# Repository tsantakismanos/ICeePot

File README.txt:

ICeePot 

GOAL
ICeePot solution is a way to help remotely accessing and managing pot moisture information. It combines several server-client technologies to gather, organize and provide moisture information in clients PC and mobile phones.

HIERARCHY
ICeePot follows the server-client architecture with the one (or several) pot server performing and saving moisture measurements and one or several mobile or desktop applications responsible for presenting moisture graphs per pot.

PROJECTS:
ICeePot/software folder contains the various projects implementing the Solutions functionality:
 - ICeePotServer: This is basically the source code of an arduino ethernet board. It reads the moisture condition from analog     pins &        saves this information on its SD card.
 - ICeePotLib: This is a library project and cointains the entities and tools used in the client Projects. It's a java project that uses        gradle to add itself in the local repository. 
 - ICeePotPC: This is a java application acting as an ICeePot client. It provides a UI to display moisture information and has dependencies    on ICeePotLib
 - ICeePotMobile: This is another ICeePot client implemented as an android application. It depens on ICeePotLib as well and provides           moisture aggregated information.
 - ICeePotWeb: This is soon to be another ICeePot client aimed to act as both a web UI and a API of the ICeePotServer. It will provide a REST API for ICeePotPC and ICeePotMobile clients which now contact directly ICeePotServer with the use of ICeePotLib

DOCUMENTATION:
ICeePot/documentation folder contains useful notes, diagrams about the project
  - notes: about tools used, code explanations, etc 
  - diagrams: flows, schematics, class diagrams, etc

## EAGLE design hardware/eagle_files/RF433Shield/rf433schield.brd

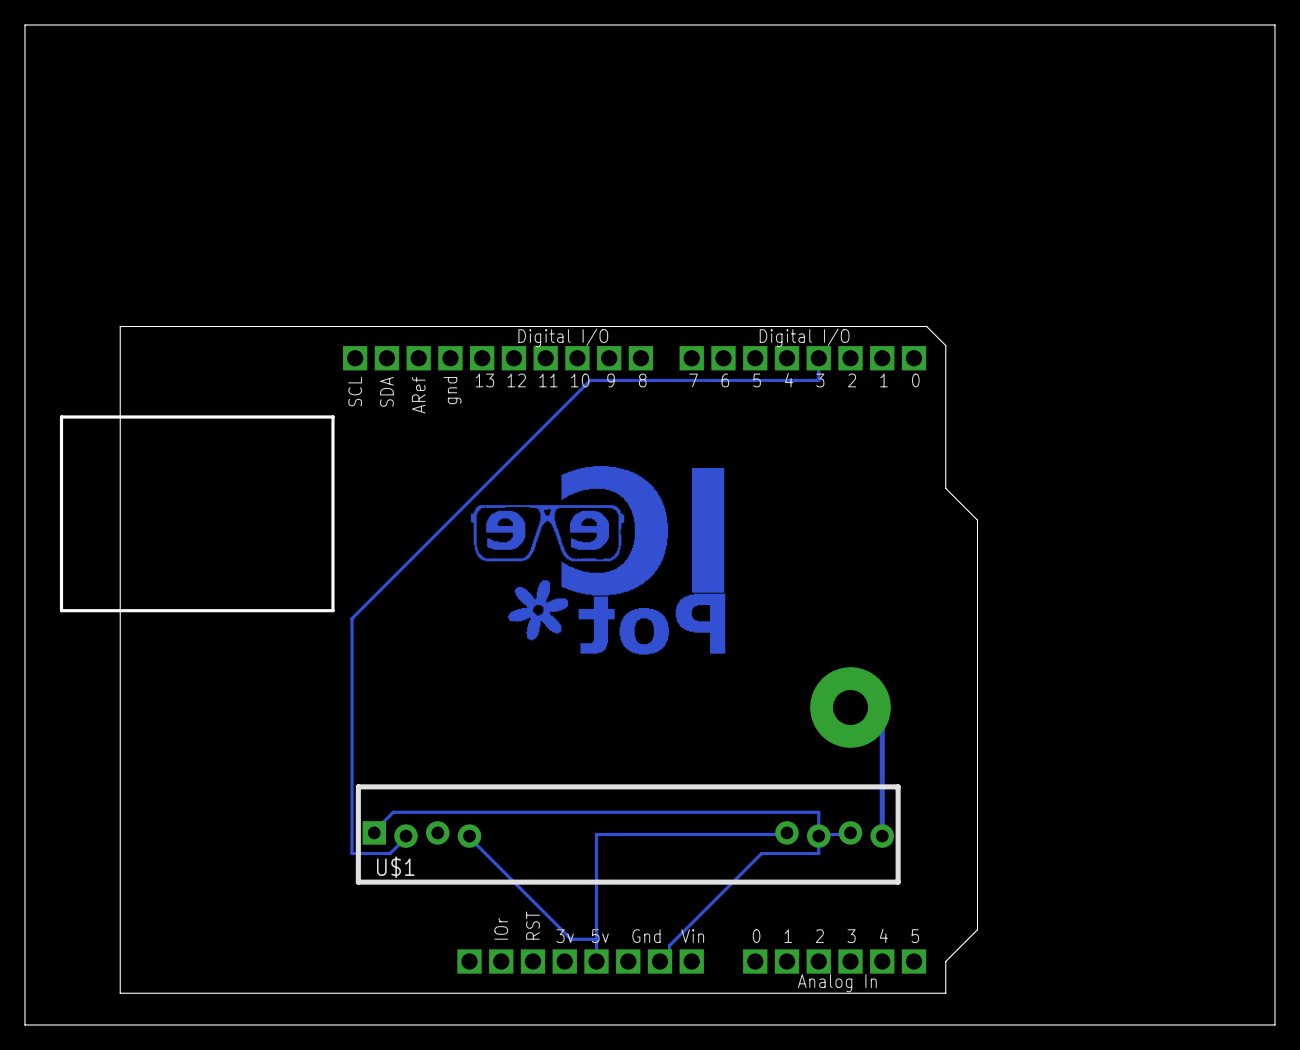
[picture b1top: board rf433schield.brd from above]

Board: 2 copper layers, 100.0 x 80.0 mm, 3 parts (0 on the bottom side), 3 nets.

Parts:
E$1: ICEEPOT_LOGO_REV
U1: ARDUINOR3-DIMENSION; ARDUINOR3
U$1: RF-LINK_RX

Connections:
unnamed: U1.D3, U$1.DATA@1
unnamed: U1.5V, U$1.+5V@1, U$1.+5V@2
unnamed: U1.GND1, U$1.GND@1, U$1.GND@2, U$1.GND@3

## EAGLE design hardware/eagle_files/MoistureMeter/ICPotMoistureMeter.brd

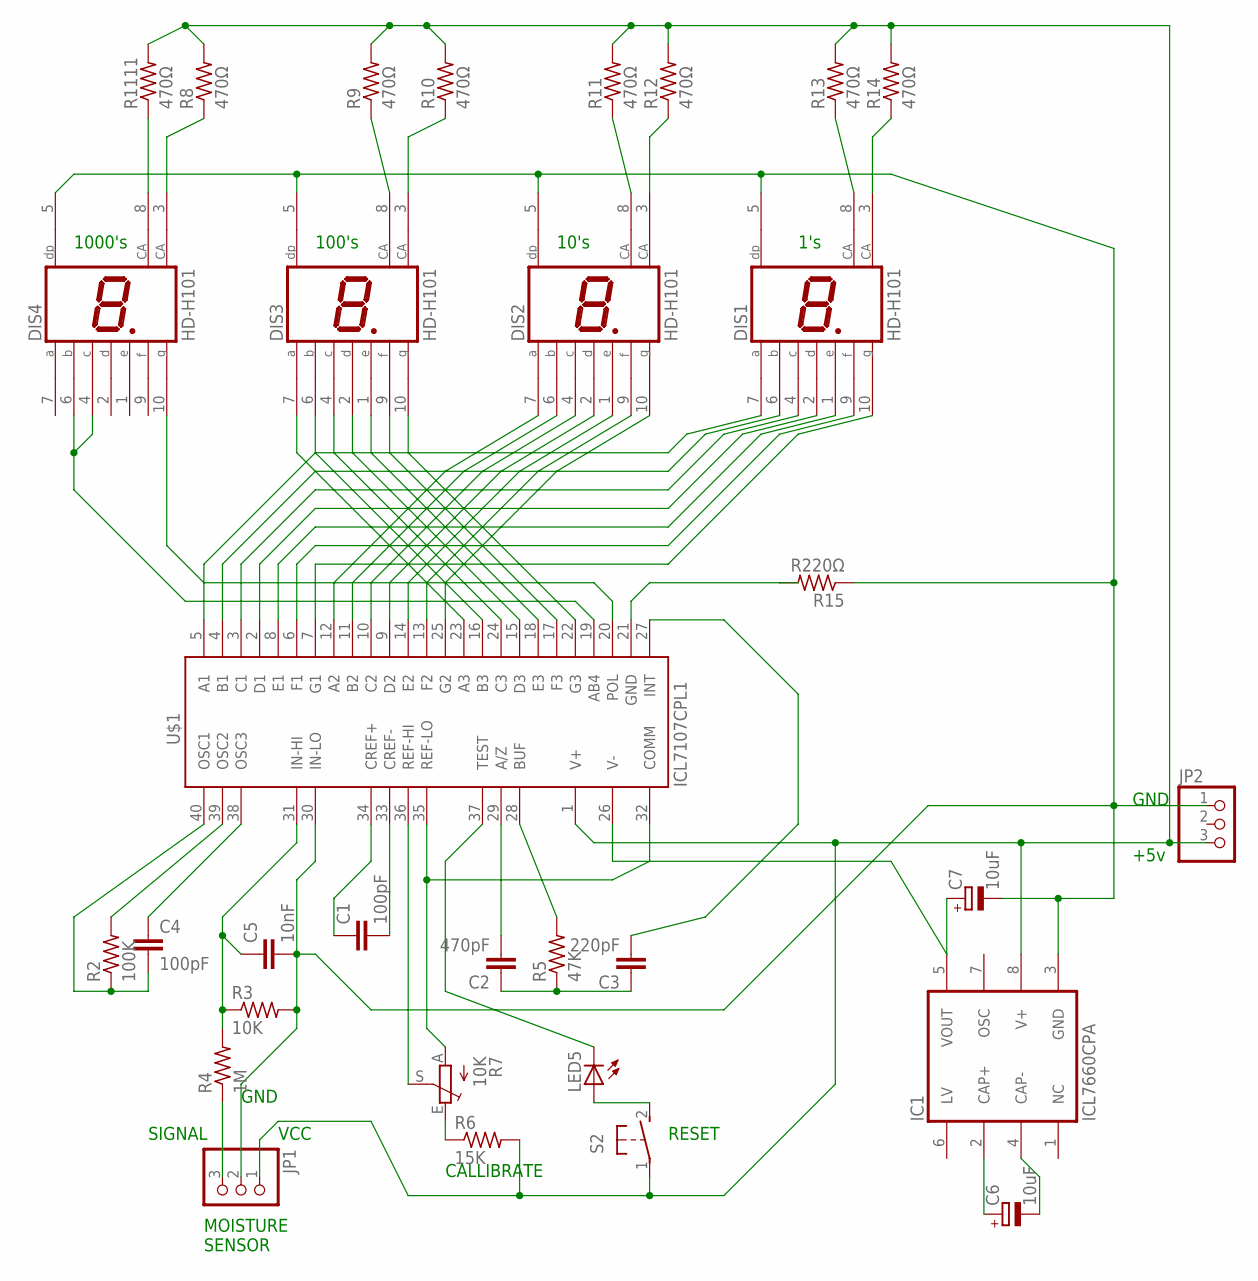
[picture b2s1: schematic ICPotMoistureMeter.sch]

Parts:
C1, C4: 100pF; C025-024X044
C2: 470pF; C025-024X044
C3: 220pF; C025-024X044
C5: 10nF; C025-024X044
C6, C7: 10uF; E2-5
DIS1, DIS2, DIS3, DIS4: HD-H101; HDSP-M
IC1: ICL7660CPA; DIL08
JP1, JP2: PINHD-1X3/90; 1X03/90
LED5: LED3MM
R2: 100K; 0204V
R3: 10K; 0204V
R4: 1M; 0204V
R5: 47K; 0204V
R6: 15K; 0204V
R7: 10K; CA6V
R8, R9, R10, R11, R12, R13, R14, R1111: 470Ω; 0204V
R15: R220Ω; 0204V
S2: 31-XX; B3F-31XX
U$1: ICL7107CPL1; DIL40

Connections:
unnamed: DIS1.7 (A), U$1.5 (A1)
unnamed: DIS1.6 (B), U$1.4 (B1)
unnamed: DIS1.4 (C), U$1.3 (C1)
unnamed: DIS1.2 (D), U$1.2 (D1)
unnamed: DIS1.1 (E), U$1.8 (E1)
unnamed: DIS1.9 (F), U$1.6 (F1)
unnamed: DIS1.10 (G), U$1.7 (G1)
unnamed: R2.2, U$1.39 (OSC2)
unnamed: C1.1, U$1.34 (CREF+)
unnamed: DIS2.7 (A), U$1.12 (A2)
unnamed: C5.1, R3.1, R4.2, U$1.31 (IN-HI)
unnamed: DIS2.6 (B), U$1.11 (B2)
unnamed: DIS2.4 (C), U$1.10 (C2)
unnamed: JP1.3, R4.1
unnamed: DIS2.2 (D), U$1.9 (D2)
unnamed: DIS2.1 (E), U$1.14 (E2)
unnamed: DIS2.9 (F), U$1.13 (F2)
unnamed: DIS2.10 (G), U$1.25 (G2)
unnamed: DIS3.7 (A), U$1.23 (A3)
unnamed: DIS3.6 (B), U$1.16 (B3)
unnamed: C1.2, U$1.33 (CREF-)
unnamed: DIS3.4 (C), U$1.24 (C3)
unnamed: DIS3.2 (D), U$1.15 (D3)
unnamed: DIS3.1 (E), U$1.18 (E3)
unnamed: DIS3.9 (F), U$1.17 (F3)
unnamed: DIS3.10 (G), U$1.22 (G3)
unnamed: C4.2, R2.1, U$1.40 (OSC1)
unnamed: DIS4.4 (C), DIS4.6 (B), U$1.19 (AB4)
unnamed: DIS4.10 (G), U$1.20 (POL)
unnamed: DIS4.8 (CA), R1111.1
unnamed: C3.2, U$1.27 (INT)
unnamed: DIS4.3 (CA), R8.1
unnamed: DIS3.8 (CA), R9.1
unnamed: DIS3.3 (CA), R10.1
unnamed: R5.2, U$1.28 (BUF)
unnamed: C4.1, U$1.38 (OSC3)
unnamed: C2.1, C3.1, R5.1
unnamed: C2.2, U$1.29 (A/Z)
unnamed: C7.+, IC1.5 (VOUT), U$1.26 (V-)
unnamed: C5.2, C7.-, DIS1.5 (DP), DIS2.5 (DP), DIS3.5 (DP), DIS4.5 (DP), IC1.3 (GND), JP1.2, JP2.1, R3.2, R15.1, U$1.30 (IN-LO)
unnamed: R7.A, U$1.32 (COMM), U$1.35 (REF-LO)
unnamed: R7.S, U$1.36 (REF-HI)
unnamed: LED5.K (C), U$1.37 (TEST)
unnamed: R6.1, R7.E
unnamed: DIS2.8 (CA), R11.1
unnamed: DIS2.3 (CA), R12.1
unnamed: DIS1.8 (CA), R13.1
unnamed: DIS1.3 (CA), R14.1
unnamed: LED5.A, S2.2 (S)
unnamed: R15.2, U$1.21 (GND)
unnamed: IC1.8 (V+), JP1.1, JP2.3, R6.2, R8.2, R9.2, R10.2, R11.2, R12.2, R13.2, R14.2, R1111.2, S2.1, U$1.1 (V+)
unnamed: C6.+, IC1.2 (CAP+)
unnamed: C6.-, IC1.4 (CAP-)

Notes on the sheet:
GND
VCC
SIGNAL
+5v
MOISTURE SENSOR
1's
10's
100's
1000's
CALLIBRATE
RESET

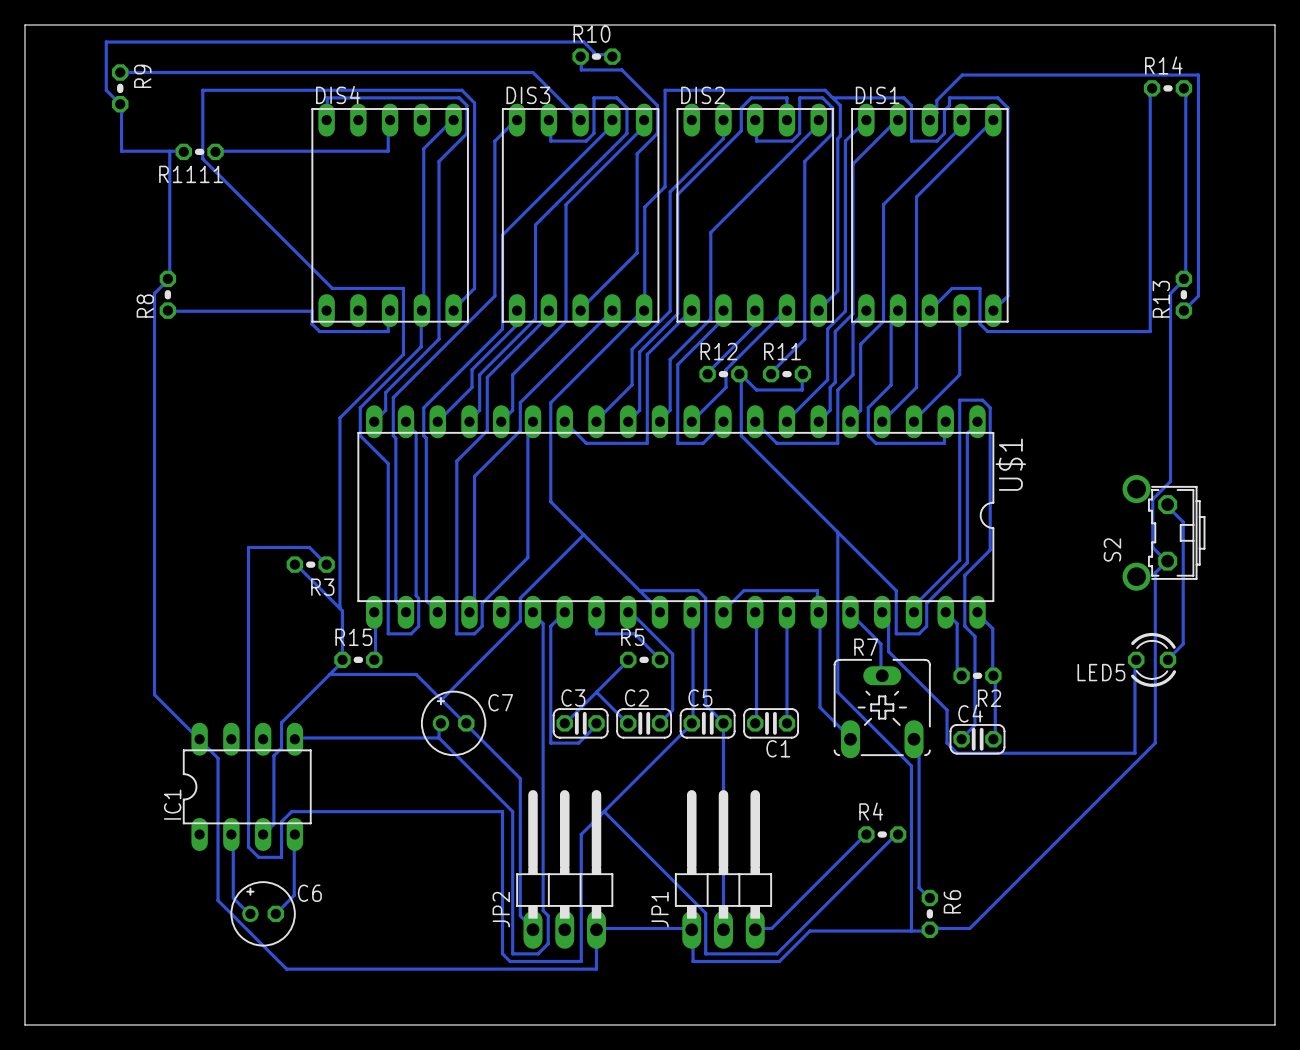
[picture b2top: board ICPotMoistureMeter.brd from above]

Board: 2 copper layers, 100.0 x 80.0 mm, 32 parts (0 on the bottom side), 53 nets.

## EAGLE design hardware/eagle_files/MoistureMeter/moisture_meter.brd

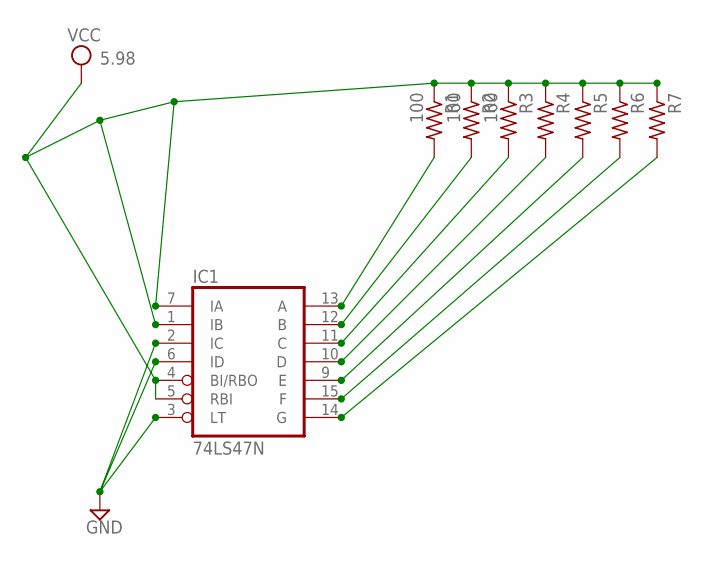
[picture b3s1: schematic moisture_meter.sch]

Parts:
IC1: 74LS47N; DIL16
R1, R2, R3: 100; 0207/10
R4, R5, R6, R7: R-US_0207/10; 0207/10

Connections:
GND: IC1.2 (IC), IC1.3 (LT), IC1.6 (ID), IC1.8 (GND)
unnamed: IC1.13 (A), R1.2
unnamed: IC1.12 (B), R2.2
unnamed: IC1.11 (C), R3.2
unnamed: IC1.10 (D), R4.2
unnamed: IC1.9 (E), R5.2
unnamed: IC1.15 (F), R6.2
unnamed: IC1.14 (G), R7.2
VCC: IC1.1 (IB), IC1.4 (BI/RBO), IC1.5 (RBI), IC1.7 (IA), IC1.16 (VCC), R1.1, R2.1, R3.1, R4.1, R5.1, R6.1, R7.1

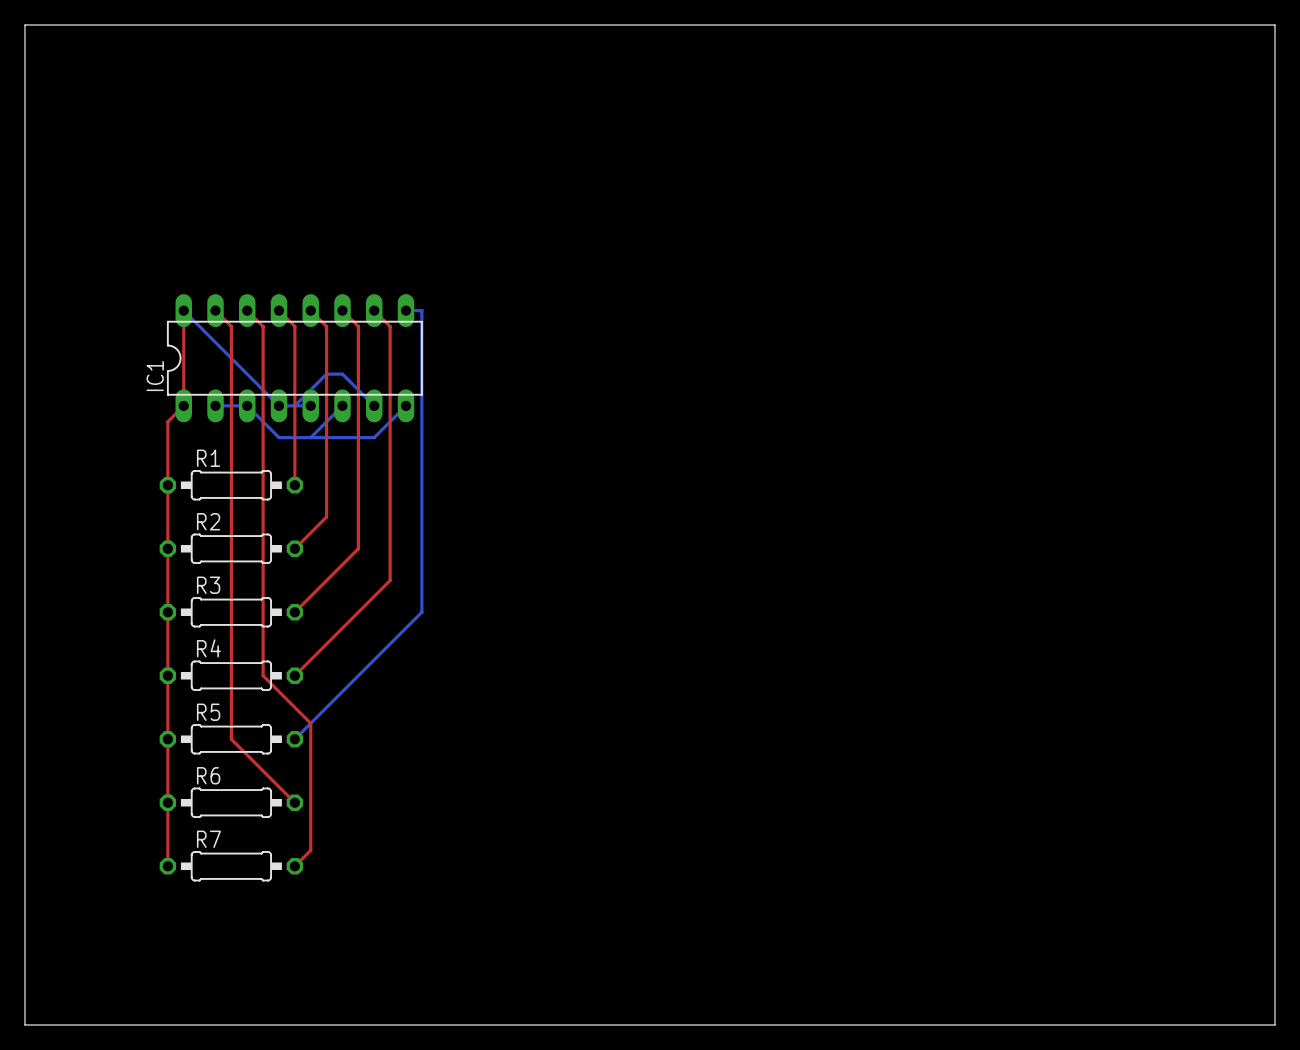
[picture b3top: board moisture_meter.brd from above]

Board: 2 copper layers, 100.0 x 80.0 mm, 8 parts (0 on the bottom side), 9 nets.

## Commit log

2013-01-16 tsantakis manos: initial commit
2013-01-16 tsantakismanos : test commit
2013-01-16 tsantakismanos: README added
2013-01-16 tsantakismanos added the first server sketch with no time synchronization
2013-01-16 tsantakismanos: arduino sketch & README
2013-01-17 tsantakismanos: README updated
2013-01-17 README updated
2013-01-17 diagram remote
2013-01-17 1 diagram removed
2013-01-17 tsantakismanos: diagrams/logos added
2013-01-17 documentation updates
2013-01-17 tsantakismanos: minor variable definitions changes in server
2013-01-17 tsantakismanos: ICeePot implemented in java swing
2013-01-18 tsantakismanos: modifications
2013-01-18 tsantakismanos: documentation updated
2013-01-18 added a single line as a suggestion for a new section in our documentation
2013-01-18 tsantakismanpos: documentation updated
2013-01-18 squash! Revert "added a single line as a suggestion for a new section in our documentation"
2013-01-18 Merge branch 'master' of https://github.com/tsantakismanos/ICeePot
    Conflicts:
    documentation/notes/git.odt
2013-01-18 tsantakismanos: files removed
2013-01-18 added the eagle project for the Moisture Meter
2013-01-18 git notes updated
2013-01-18 swing client implemented
2013-01-19 changes in software workspace file organizing
2013-01-21 swing_client mockup added
2013-01-23 changes in subproject names
2013-01-24 diagrams added
2013-01-24 diagrams added & others renamed
2013-01-25 ICeePotServer flow diagram modified
2013-01-25 measurement files are now organized in date basis (1 per month) and the files are named after that day
2013-01-25 modifications for better printing result
2013-02-01 diagram updates with new ideas about client-server messages
2013-02-01 PC client mock-up modified
2013-02-02 client now sends the desired date to server instead of dummy messages
2013-02-02 time interval between measurements changed to 15 minutes
2013-02-02 Time and NTP libraries added to the project
2013-02-04 Server time synchronized manually. File in which server stores files changed to Day|hour:minutes:sec|pin|value
2013-02-06 server is now able to time-synchronize itself at the beggining of the sketch
2013-02-07 ICeePotPC: a package created to model the server communication and the UI package modified to meet this change
2013-02-07 small modification in variable names
2013-02-07 custom NTP library updated to time-sunchronize the server
2013-02-08 documentation: organized diagrams to folders
2013-02-12 Date selectors added to MainWindow & Alert Dialog added
2013-02-12 debug precompiler declaration removed
2013-02-12 first request to server with dates set from MainWindow
2013-02-13 new pots added, and alerts
2013-02-13 minor bugs in message parsing
2013-02-13 minor bug in message parsing
2013-02-13 unnecessary file
2013-02-14 Results area moved into a Scrollable Pane
2013-02-14 main window set to non-resizable
2013-02-14 pot panel is now the swing entity to be displayed in every tab
2013-02-14 interval in server changed to 20 mins
2013-02-14 last measurement text boxes enabled
2013-02-15 chart creation
2013-02-17 comments removed, debug options added in context for showing/hiding the results panel and from-to dates information retrieval from server is now available
2013-02-17 return nothing is month info not available
2013-02-19 adding pots & server settings now moved to a config file. Adding pots is now possible
2013-02-19 icon into jar, exception handling in addpot, change server
2013-02-19 debug-->false, time interval=60min
2013-02-20 changed the format in latest measurement date
2013-02-20 dateformat variable for potpanel as class variable, textresults now show the whole date
2013-02-21 handler added for dropdowns be more responsive and window sizes changed
2013-02-22 sanity checks if pots are available in the settings.file
2013-02-22 Dynamical adding tabs when NewPot is done. This is done with the use of Observer pattern to MainWIndow
2013-02-22 Context object now follows the Singleton pattern, class diagram also added
2013-02-27 resizable UI
2013-02-27 settings xml creation if non-existent in the beginning
2013-02-27 bug fixed, now measurements are fetched per pot analog pin (not all)
2013-02-27 resized the results list text area
2013-02-27 resizings..
2013-02-28 settings.xml with no caps and Jchart panel resizable to both directions
2013-02-28 new jar
2013-03-01 bug fixed txtresults gets cleared in every "Get info" click
2013-03-01 server sketch (minor TODOs), new client jar
2013-03-06 separate thread in PotPanel UI for request execution, progressbar added and min - max series added to chart
2013-03-08 progressbar shows real progress, closings in window more efficient
2013-03-08 server can now update its time periodically
2013-03-08 settings shouldn't be in repository
2013-03-08 settings.xml to be ignored from now on
2013-03-12 slidebars added to pot panels for setting min/max moist values, Server timeout also in settings
2013-03-12 Handling for settings xml moved from context to a special Settings class, Exception handling changed in context class
2013-03-12 minor bug fixed on the slidebars size, hostname is not validated in settings dialog
2013-03-12 Application jar moved to bin folder (unversioned)
2013-03-12 server request done from separate thread of the newly class ThreadService
2013-03-14 appication packege renamed to application
2013-03-14 ServerService run method now passes an Exception to its caller if the request itself throws one
2013-03-22 server connection modifications
2013-03-22 the schematic for RF shield which will be the RF interface of the arduino server
2013-03-22 unnecessary handler removed
2013-03-31 Pin concept replaced with id one. Fixed bug to update the moist values of the right pot
2013-04-03 wireless mode added to server sketch, virtual library added and chart jar added to client
2013-04-11 COntext passing as argument replaced with calls to static getInstance method
2013-04-11 Pot object removed from UI elements and now only Context keeps them in an Array, providing methods for accessing them to UI
2013-04-11 Pot concept in server package turned to potId (just renaming).
2013-04-11 server sketch and swing client changed to store/receive/parse binary packets instead of text ones. Type of measurement also added as a concept
2013-04-11 changes to documentation
2013-04-12 bugs fixed, comments removed, time server changed
2013-04-12 bug fixed: in packet receiving
2013-04-12 pot creation moved from NewPotDialog to Context method, check if ID given is unique
2013-04-12 server script to migrate text measures to binary ones
2013-04-12 bugs in migr script
2013-04-13 migration script executed
2013-04-13 migration script final
2013-04-14 unnecessary swing component variables removed after code review
2013-04-17 remove pot funcitonality added
2013-04-19 Simple/Detail view mode added
2013-04-28 Latest schematic updates and the pcb design
2013-04-28 rfshield and transmitter schematics added
2013-04-28 rfshield and tansmitter added
2013-04-28 rfshield epf file options
2013-04-28 The Gimp project files for creating the actual pcb print page with 4 rfpic pcb instances on it
2013-05-14 Minor change in README file
2013-09-04 Deleted not required save files
2013-09-04 New version
2013-09-04 sensor image added to overall diagram
2013-09-04 Nicer placement on the schematic
2013-09-08 Added ICeePot logo on the copper of the board
2013-09-08 Added rfpic transmitter assembly code
2013-11-03 Added PCB Antenna on the transmitter board
2015-09-05 initial commit for ICeePotMobile
2015-09-15 Modified Pot class to be ready to get removed
2015-09-15 Added new project to server as a library
2015-09-15 Removed Pot entity and replaced from ICeePotLib project
2015-09-21 Moved Callable interface from application package to servergw package
2015-09-21 changed build tools version
2015-09-21 Added mockups for ICeePotMobile
2015-09-21 Moved server communication functionality from ICeePotPC to ICeePotLib
2015-09-21 Transformed lib project to gradle project
2015-09-26 Published ICeePotLib project to local folder Added dependency to ICeePotMobile
2015-09-26 Reorganized mockups
2015-09-26 Organized packages, created dbhelper and the first version of main
2015-09-27 Added default constructor in Pot class
2015-10-09 Loaded pots in main screen
2015-10-10 Added icon
2015-10-11 Added New Pot activity
2015-10-15 Added saving pot functionality
2015-10-15 modifications to gitignore
2015-10-15 the right one
2015-10-15 reversed
2015-10-15 added vcs configuration for android studio
2015-10-15 Reloaded Pots in Main, Added Dialog for warnings
2015-10-20 Generic Dialog class created to handle all dialog needs
2015-10-28 New Pot activity started in every pot list click
2015-11-06 Added chart in Mobile, with the required changes in Library
2015-11-06 deleted logs
2015-11-07 Finished first verion of moisture graph
2015-11-12 fixed graph bugs
2015-11-15 Added settings as shared preferences
2015-11-28 applied first basic styling
2015-11-28 graph styling
2016-01-13 refactor-renamed server related entities
2016-01-28 README rewritten
2016-02-14 minor commit
2016-02-14 Measurement class moved to entities packace
2016-02-14 Changed .gitignore, Added new Web project
2016-02-17 first mvc configuration
2016-02-19 First controller, model and test
2016-02-20 Created and Tested REST mock controller
2016-02-21 Added/Tested RemoteSource implmementation
2016-02-21 Removed Type from Measurement
2016-02-21 Controller to return HashMap
2016-02-23 Added/Tested Source in COntroller
2016-02-26 Created additional config profiles, Added exception handling in controller
2016-03-12 changed dependency servlet-api
2016-03-27 first dummy deployable version
2016-03-27 removed hello page and view
2016-04-02 untracked gradle error logs
2016-04-02 added resttemplate call
2016-04-03 Changed Controller to return Measurements instead of HashMaps
2016-04-03 Changed mobile to read measurement list
2016-04-03 Added jackson dependency
2016-09-04 diagram for caching
2016-09-04 Refactored Source and RemoteSource and added new entities
2016-09-07 Added cache support
2016-09-09 removed unneccesary idea files
2016-09-09 removed uneccessary iml files
2016-09-09 Removed iml file, changed android SDK build tools
2016-09-09 Excluded lint checn in build
2016-09-11 Enhanced api with validations
2016-09-17 Added current moisture feature to web api
